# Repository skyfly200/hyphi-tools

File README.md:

# Hyphi Tools

Browser-based design tools for Hyphi's LED art, origami and print work, plus
the hardware pipeline for Hyphi boards. The web app is a single Vite build:
a React router shell, with the larger editors written in Vue and mounted
inside it. Everything runs client-side; there is no backend.

## Tools

| Route | Tool | What it does | Exports |
|-------|------|--------------|---------|
| `/qr` | **QRForge** | Styled QR codes: colors, dot shapes, logos, frames, many payload types (URL, Wi-Fi, vCard, SMS, ...), UTM campaign tags on URLs | PNG, JPG, SVG, multi-part STL zip for multi-material printing |
| `/fold` | **FoldPress** | Turns a `.fold` or SVG crease pattern into a pair of press plates for pre-creasing paper | STL |
| `/foldform` | **FoldForm** | Living-hinge origami models: rigid panels with flexible fold lines, optional SVG artwork as a multi-color design layer | STL zip (model plus front/back design layers) |
| `/foldstudio` | **FoldStudio** | Crease pattern editor on a dynamic grid with mirror, repeat and angle-defined creases; checks flat-foldability | FOLD |
| `/foldstudio/docs` | FoldStudio docs | User guide for FoldStudio | |
| `/polyforge` | **PolyForge** | Parametric polyhedral LED fixtures: pick a solid, set design rules, place LEDs and connectors, unfold to a flat PCB | DXF and KiCad board for fab, GLB/STL of the folded model, patch JSON |
| `/harness` | **Harness Calculator** | Plans LED stem wiring harnesses (core bends, power taps, data links, tip forks, wire twist) and builds a precut wire list | CSV cut list, GLB of the 3D view |

The home page (`/`) links to each tool, plus the link shortener at
[l.hyphi.art](https://l.hyphi.art), which lives in the `hyphi-links` repo.

FOLD-based tools hand designs to each other ("Open in ...") through
`sessionStorage`, and save projects and preferences to `localStorage`, so
nothing leaves the browser.

## Development

Needs Node 18+ (developed on Node 22).

```sh
npm install
npm run dev       # Vite dev server
npm run build     # production build into dist/
npm run preview   # serve the built dist/
```

Netlify builds with `npm run build`, publishes `dist/`, and rewrites every
path to `index.html` so client-side routes work (see `netlify.toml`).

## Layout

```
src/
  main.jsx, App.jsx        React entry and routes
  Home.jsx                 landing page / tool index
  QRForge.jsx              React tools (single-file components)
  FoldPress.jsx
  FoldForm.jsx
  FoldStudioDocs.jsx
  FoldStudio.jsx           React wrappers that mount a Vue app ("Vue islands")
  PolyForge.jsx
  HarnessCalculator.jsx
  foldstudio/              FoldStudio Vue app: components/, lib/ (geometry, FOLD I/O, faces, persistence)
  polyforge/               PolyForge Vue app: components/, lib/ (polyhedra, unfold, LEDs, DXF, KiCad, zip)
  harness/                 Harness Calculator Vue app (Vuetify) and 3D view
  lib/                     shared helpers: FOLD handoff, FoldForm persistence, crease palette
QRForge/                   earlier standalone drafts of the QR generator (not part of the build)
hardware/                  KiCad/Blender hardware pipeline (Python, not part of the web build)
```

To add a tool, create its component in `src/`, add a `<Route>` in
`src/App.jsx`, and add a card to the `TOOLS` list in `src/Home.jsx`. For a
Vue tool, follow the pattern in `src/PolyForge.jsx`: a React component that
owns a host `div` and dynamically imports a `mount.js` that mounts the Vue app
into it, so Vue only loads on that route.

## Hardware pipeline

`hardware/` holds the spec-driven KiCad pipeline for Hyphi boards (migrating
off EasyEDA): one `product.yaml` per product, a parts library builder
(`fetch_parts.py`, using `easyeda2kicad`) and a headless Blender renderer
(`render.py`). It's Python and runs separately from the web app. See
[hardware/README.md](hardware/README.md) for phases and setup.

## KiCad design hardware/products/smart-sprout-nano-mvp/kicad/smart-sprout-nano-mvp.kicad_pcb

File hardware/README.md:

# Hyphi Hardware

Spec-driven KiCad pipeline for Hyphi boards. One `product.yaml` per product is
the source of truth; scripts turn it into libraries, netlists, layouts,
enclosures and build receipts. Deliberately semi-automated: scripts do the
repeatable parts, a human routes the critical nets and signs off.

```
hardware/
  products/<product>/product.yaml   spec: outline, parts (LCSC), placement, enclosure, variants
  products/<product>/kicad/         KiCad project (imported or generated)
  libs/hyphi/                       project symbol/footprint/3D library (built from specs)
  scripts/                          pipeline scripts (fetch_parts.py, altium_to_spec.py, check_board.py, render.py)
  docs/                             how-tos
```

## Phases

| Phase | Goal | Status |
|-------|------|--------|
| 0 | Migrate GlowFlora Home (V2 prototype) from EasyEDA to KiCad, install JLCPCB tooling, draft the spec | **in progress** |
| 1 | Spec-to-netlist proof (SKiDL) on one subcircuit: the MT9700 current-limit section | not started |
| 2 | Board-to-enclosure: Build123d for the printable shell (STEP/STL), Blender for organic parts and renders, both reading the spec and the KiCad board export | render script ready |
| 3 | CI gates: `kicad-cli` ERC/DRC, Gerber/BOM/CPL export, LCSC pricing, cost rollup | not started |
| 4 | Generative variants from one spec | not started |

## Products

| Product | Spec | Source |
|---------|------|--------|
| Smart Sprout Nano MVP | [product.yaml](products/smart-sprout-nano-mvp/product.yaml) | spec generated from the EasyEDA Pro Altium export; [KiCad project](products/smart-sprout-nano-mvp/kicad/) imported in KiCad 10; `check_board.py` passes |
| GlowFlora Home | [product.yaml](products/glowflora-home/product.yaml) | hand-seeded from the wiki BOM |

To draft a spec for another board from an EasyEDA Pro Altium export:

```sh
python3 hardware/scripts/altium_to_spec.py "<export>/Smart Sprout/<board folder>" \
  --id <product-id> --name "<Product Name>" --out hardware/products/<product-id>/product.yaml
```

Check a KiCad board still matches its spec (outline, layer count, every
part's position, rotation and side; no KiCad install needed):

```sh
python3 hardware/scripts/check_board.py hardware/products/<id>/product.yaml hardware/products/<id>/kicad/<id>.kicad_pcb
```

## Phase 0 quick start

1. Follow [docs/phase0-migration.md](docs/phase0-migration.md) to install KiCad 10
   and the plugins and import the EasyEDA project.
2. Build the project parts library from the spec:

   ```sh
   pip install easyeda2kicad pyyaml
   python3 hardware/scripts/fetch_parts.py hardware/products/glowflora-home/product.yaml
   ```

   This runs `easyeda2kicad` for every LCSC part in the spec and writes
   symbols, footprints and STEP models into `hardware/libs/hyphi/`. It needs
   internet access to the EasyEDA/LCSC API.
3. `python3 hardware/scripts/fetch_parts.py --check <product.yaml>` validates the
   spec and prints the Basic/Extended part split without downloading anything.

## Blender

KiCad stays the source of the board; Blender consumes it. The split:

- **Build123d** makes anything that must fit and print (shell, battery bay,
  switch and USB openings), because its dimensions come straight from the spec.
- **Blender** handles organic or decorative geometry (petals, diffusers, the
  sculpted parts of a GlowFlora) and every render, so photos and geometry come
  from the same files.

Render the board (and any Blender-authored models listed under `render.models`):

```sh
kicad-cli pcb export glb --subst-models --include-tracks --include-pads \
  -o hardware/products/glowflora-home/kicad/glowflora-home.glb \
  hardware/products/glowflora-home/kicad/glowflora-home.kicad_pcb
pip install bpy pyyaml
python3 hardware/scripts/render.py hardware/products/glowflora-home/product.yaml --variant default
```

PNGs land in `products/<product>/build/renders/`. A variant can override any
`render` field, for example a different enclosure model or camera list.

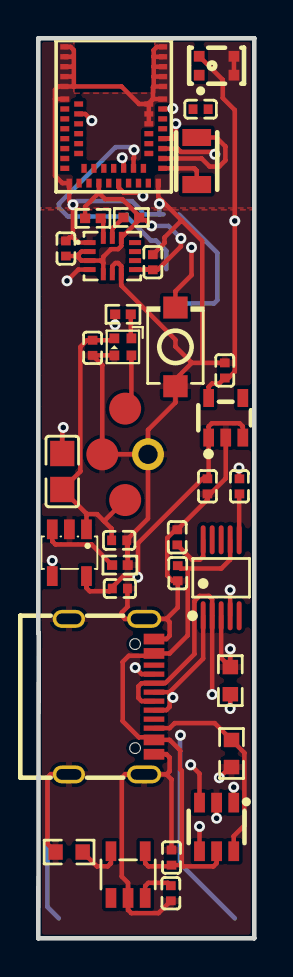
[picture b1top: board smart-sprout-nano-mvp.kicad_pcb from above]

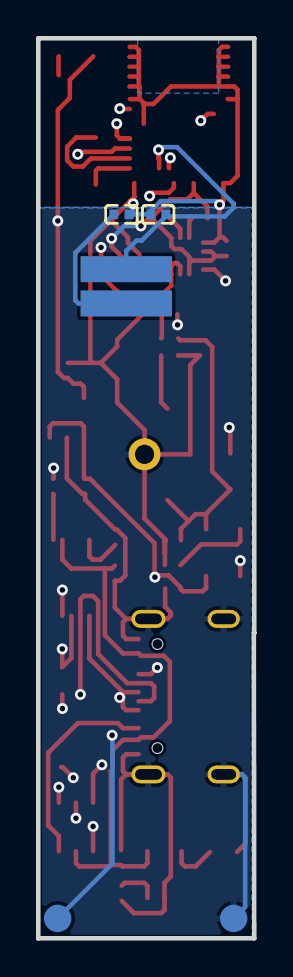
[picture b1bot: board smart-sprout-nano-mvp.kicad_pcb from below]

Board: 4 copper layers, 12.0 x 50.0 mm, 35 parts (2 on the bottom side), 27 nets.

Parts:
APP: SW-SMD_L3.9-W3.0-P4.45
C1, C2, C4, C5, C6, C7, C8, C9, C10, C11, C12, C13, C14, C15, C16: C0402
C3: C0805
D1: SOT-23-6_L2.9-W1.6-P0.95-LS2.8-BR
LED1: LED-SMD_4P-L1.5-W1.5-BL
M1: AN54LV-15
MIC1: MIC-SMD_4P-L2.8-W1.9-P1.84-TL_ZTS6117
R1, R2, R10: R0603
R6, R7, R14, R15: R0402
U1: MSOP-10_L3.0-W3.0-P0.50-LS5.0-BL
U2: SOT-23-5_L2.9-W1.6-P0.95-LS2.8-TL
U3: SOT-23-5_L3.0-W1.7-P0.95-LS2.8-BR
U4: SOT-23-5_L2.9-W1.6-P0.95-LS2.8-BR
U5: LGA-14_L3.0-W2.5-P0.50-TL
USB1: USB-C-SMD_GT-USB-7010E
X1: CRYSTAL-SMD_L3.2-W1.5

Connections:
$1N6708: LED1.1, R6.1
$1N12565: M1.24, R6.2
$1N16326: M1.25, U3.4
$1N17706: M1.33, X1.1
$1N17711: M1.32, X1.2
$1N18487: APP.2, M1.37
$1N18941: R7.1, U3.3
$1N18953: C13.1, M1.43
$2N1: D1.3, U1.1, USB1.A6, USB1.B6
$2N2: D1.1, U1.2, USB1.A7, USB1.B7
$2N11: R1.2, U2.5
$2N14: D1.6, R10.2, USB1.B5
$2N15: D1.4, R2.2, USB1.A5
$2N21: C10.2, U1.10
+5V: C4.1, C7.2, D1.5, U1.7, U2.4, USB1.A4B9, USB1.B4A9
DTR#: C13.2, U1.6
GND: APP.1, C1.2, C2.1, C3.1, C4.2, C5.2, C6.2, C7.1, C8.1, C9.1, C10.1, C11.1, C12.1, C14.1, C15.1, D1.2, LED1.3, M1.1, M1.15, M1.31, M1.40, M1.42, M1.44, M1.45, M1.46, M1.47, M1.48, M1.49, M1.50, M1.51, M1.52, M1.53, M1.54, M1.55, MIC1.2, MIC1.3, R1.1, R2.1, R7.2, R10.1, U1.3, U2.2, U3.2, U4.2, U5.1, U5.6, U5.7, USB1.1, USB1.2, USB1.3, USB1.4, USB1.A1B12, USB1.B1A12
INT1: M1.4, U5.4
NFC1: C8.2, M1.29
NFC2: C9.2, M1.27
RTS#: M1.35, U1.4
SCL: R14.2, U5.13
SDA: R15.2, U5.14
VBAT: C6.1, U2.3
VBATT: C1.1, C14.2, U3.5, U4.1, U4.3
VCC: C11.2, C12.2, C15.2, M1.20, MIC1.4, R14.1, R15.1, U4.5, U5.2, U5.3, U5.5, U5.8, U5.12
VLED: C2.2, C3.2, C5.1, LED1.2, U3.1

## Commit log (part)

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2026-04-16 Add QRForge tool
2026-04-17 Add .gitignore for node_modules and dist
    https://claude.ai/code/session_01VfCD3NQzr8GGxB5WpyrceK
2026-04-17 Add spacing between card name and subtitle
    https://claude.ai/code/session_01VfCD3NQzr8GGxB5WpyrceK
2026-04-17 Remove false no-tracking claim from link shortener card
    https://claude.ai/code/session_01VfCD3NQzr8GGxB5WpyrceK
2026-04-18 Make footer hyphi.art a link
    https://claude.ai/code/session_01VfCD3NQzr8GGxB5WpyrceK
2026-04-18 Read shortUrl param name from link shortener callback
    https://claude.ai/code/session_01VfCD3NQzr8GGxB5WpyrceK
2026-04-18 Fix logo transparency, icon visibility, grid width, and default preset
    - Skip QR dots in logo bounding box so icons render cleanly with no modules bleeding through
    - Icon cards in unselected state now use #ddddf0 (always-visible) instead of fgColor which could be black-on-black
    - Icon grid switched from 4 to 5 columns with tighter padding for narrower cards
    - Added "Default" (white on black) as the first color preset
    https://claude.ai/code/session_01VfCD3NQzr8GGxB5WpyrceK
2026-04-18 Embed icon SVGs inline; no image wrappers or backgrounds
    - Replace svgToDataURL with extractSVGInner (strips <svg> wrapper only)
    - Add IconSVG component that renders paths inline with color via CSS currentColor
    - Icon selection sets selectedIcon only; logo state is now custom-upload-only
    - buildSVG embeds icons as a scaled <g> with inline paths; <image> only for uploads
    - inLogo guard now checks logoEnabled && (logo || selectedIcon)
    - Logo controls (color, size, notice) conditioned on logo || selectedIcon
2026-04-18 Export multi-material STL as a zip with two separate files
    - generateSTL now returns {base, modules} instead of a combined string
    - makeZip: pure-JS ZIP writer (STORE method, CRC-32, no deps)
    - Multi-material download: qrcode.zip containing qrcode_base.stl + qrcode_modules.stl
    - Single-material download unchanged: qrcode.stl
    https://claude.ai/code/session_01VfCD3NQzr8GGxB5WpyrceK
2026-04-21 FoldPress: heightfield plates with proper ridges and grooves
    - Replaced ridge-only prism approach with a 200×200 heightfield grid per plate
    - Top plate: M=ridge, V=groove; Bottom plate: V=ridge, M=groove; F/U=ridge both
    - Clearance gaps only at vertices shared by both M and V edges (not every intersection)
    - Output is binary STL (50 bytes/tri) instead of ASCII — ~4MB per plate vs ~12MB
    - makeZip already handles Uint8Array so no changes needed there
    https://claude.ai/code/session_01VfCD3NQzr8GGxB5WpyrceK
2026-04-21 FoldPress: fix anti-diagonal triangulation spikes in STL
    Standard quad triangulation splits every cell along the (0,0)→(1,1)
    diagonal. When a fold line runs along the opposite diagonal, adjacent
    triangles get wildly mismatched heights, producing saw-tooth spikes.
    Fix: choose the split diagonal per cell so the edge with the smaller
    height difference is used as the shared axis.
    https://claude.ai/code/session_01VfCD3NQzr8GGxB5WpyrceK
2026-04-21 QRForge: link Stats button to specific short-link dashboard page
    https://claude.ai/code/session_01VfCD3NQzr8GGxB5WpyrceK
2026-04-23 Add alignment rails and asymmetric keying to FoldPress
    Bottom plate gains a rectangular guide-wall frame (4 outer wall boxes)
    so the top plate slides into position automatically — no manual paper
    pre-alignment. One corner of the frame has a raised square tab; the
    matching corner of the top plate has a raised pip, making the correct
    orientation unambiguous for any pattern, including symmetric ones.
    New UI controls: Alignment rails toggle + Rail height / Wall thickness /
2026-04-25 FoldForm: auto-clamp hinge thickness to never exceed paper thickness
    useEffect reduces hingeH whenever panelH drops below it. Hinge slider
    max is bound to panelH and the number input clamps on change, so the
    constraint is enforced from all three interaction paths.
    https://claude.ai/code/session_01VfCD3NQzr8GGxB5WpyrceK
2026-04-26 FoldForm: face color painter + .fold export + Origami Simulator link
    - computeFaces(): planar half-edge traversal finds all bounded face
    regions from the crease pattern graph (works for .fold and SVG input)
    - Faces auto-assigned distinct colors from a 10-color palette on load
    - Click any panel in the preview to select it, then use the color picker
    to paint it; fold lines remain drawn on top for reference
    - toFOLD(): exports vertices, edges, faces + faces_color as a valid
2026-05-07 Add city mode, block scale, NFC pocket, border frame, edge text, multi-part export, nozzle snap, keychain placement to QRForge
    New 3D features:
    - City Mode: random per-module heights (configurable min/max) for skyscraper look
    - Block Scale: shrink module footprint 50-100% to add gaps between dots
    - Invert QR: swap dark/light modules
    - Border Frame: separate raised lip body for multi-color printing
    - NFC Pocket: recessed cavity on bottom face for embedding NFC sticker
2026-05-07 FoldStudio: square paper corners, inset paper inside canvas for edge-grab margin
2026-05-07 FoldStudio: project save/load + persistent prefs + TopBar with file controls
    - localStorage persistence for grid, labels, current paint assignment
    - Save/Open/Delete projects (named, in-browser) with modal UI
    - New TopBar holds New/Save/Open/Import/Export FOLD/Export SVG
    - Sidebar trimmed to Grid + Labels (file controls moved up)
    - Toolbar reorganized: Draw+Select with icons, separator, Mirror+Rotate+Angle with icons
    - Inline SVG icon set (Icon.vue) used by both bars
2026-05-07 FoldStudio: fix T-junctions, real Simulator handoff, radial-edge snaps
    - addEdgeWithSplits / repairPlanarGraph now split existing edges when a new
    segment terminates on the interior of one (T-junction), so face computation
    produces a complete face graph instead of just the outer paper face
    - loadModel runs repairPlanarGraph so previously-saved patterns get cleaned up
    - Open in Simulator: download the .fold and open origamisimulator.org with
    clear drop-the-file instructions (the ?pattern=data: URL was never honored
2026-05-08 FoldStudio: mobile-friendly layout
    - Sidebar and Inspector collapse to off-canvas drawers below 900px wide,
    with toolbar toggle buttons (panelLeft / panelRight) and a tap-to-dismiss
    backdrop
    - Toolbar drops tool labels and bumps padding for touch-friendly tap targets
    - TopBar drops button labels at <=700px so the file controls fit
    - Modals constrain to viewport (max-width/height with overflow-y) and the
2026-05-08 FoldStudio: make Mirror selection click-to-toggle, highlight axis edge
    - Mirror tool now treats canvas clicks like additive selection (click to add,
    click again to remove), no shift needed — works on touch
    - When Mirror axis = "Selected edge", the first selected edge is rendered
    with an orange dashed overlay so the user can see which one is the axis
    - Apply Mirror disabled until >=2 edges selected when axis=edge
    - Cleaner hint text in the Tool options drawer
2026-05-08 FoldStudio: cleanup button + shared crease palette across all fold tools
    - New src/lib/foldPalette.js exports the canonical M/V/B/F/U stroke colors
    (and OS-specific colors) plus dash style. FoldForm, FoldPress and FoldStudio
    all import from it so the same .fold pattern renders identically across
    the three tools (M red, V blue, B near-black, F gray dashed, U muted)
    - cleanupRedundant model helper iteratively merges degree-2 vertices whose
    two incident edges share an assignment and lie ~180 degrees apart, plus
2026-05-09 FoldStudio: BottomBar for file actions, merged Export, templates modal, distinct icons, brighter boundary
    - New BottomBar.vue holds project actions: New (opens template modal),
    Cleanup, Save, Open, Import, Export (single button with .fold/.svg select,
    default FOLD), Simulator, FoldForm, FoldPress
    - TopBar slimmed to: brand + project + Tools toggle (mobile) + Snap + Help
    + Info toggle (mobile). All file-flow modals removed from TopBar
    - New NewProjectModal.vue + lib/templates.js with bases: Blank,
2026-05-09 FoldStudio: move Edges/Vertices/Both segmented control to the toolbar (visible while Select tool active)
2026-05-10 FoldStudio: drop rabbit-ear, pinch-zoom, mobile tooltip, status in bottom bar, select-mode icons
    Bundle: FoldStudio JS dropped from 99.5 KB → 47.9 KB gzipped (~52% smaller).
    - Replaced rabbit-ear's graph.populate with a self-contained planar face
    traversal in lib/faces.js. Same output for the patterns we care about;
    rabbit-ear removed from package.json
    - New Tooltip.vue listens for long-press (~500ms) on any [title] element
    and shows a centered toast above the touch point. Native title is
2026-05-12 FoldForm: drop Open-in-FoldPress; FoldStudio: mobile paint dropdown
    - FoldForm: removed the Open-in-FoldPress handoff button; only
    Edit-in-FoldStudio remains in the export row
    - FoldStudio mobile (<=900px): the five M/V/B/F/U paint buttons collapse
    into a single trigger button showing the active paint + chevron. Tap to
    open a small popover with all five options (color swatch + letter + full
    name). Tap an option to pick + close; tap outside to dismiss via a tiny
2026-05-12 FoldStudio: light/dark theme toggle + outlined Help swatches
    - Help modal swatches updated to the canonical EDGE_COLOR values and now
    carry a faint white outline so the darker B / U boxes are visible
    against the modal background
    - Light/dark theme switcher in the TopBar (sun/moon icon, persisted).
    Theme classes redeclare a wider set of CSS variables — including new
    --canvas-bg, --paper, --paper-stroke, --grid-line, --grid-node, --vertex
2026-05-12 FoldStudio: docs page, label rework, multi-select toggle, validation in Sidebar
    - New /foldstudio/docs route — full-page docs with TOC, mobile vs desktop
    comparison, every feature explained. Help modal gains an "Open full
    docs ↗" link that opens in a new tab
    - Labels reworked: instead of three independent V/E/F checkboxes, one
    type at a time via a segmented control (Off / V / E / F). New
    "Hover-only" option restricts the display to the label closest to the
2026-05-13 FoldStudio bases flat-foldable, FoldForm/FoldPress download race fix, clearer relief UI
    - Templates: Preliminary, Waterbomb and Radial bases ship with valid M/V
    assignments. Each flips one crease to satisfy Maekawa (preliminary
    5V+3M, waterbomb 5M+3V, radial 9M+7V at the centre). Square twist
    remains 'U' since its geometry needs extra pleats to fold flat.
    Smoke-tested: all six templates now report OK from
    validateFlatFoldability after load
2026-05-13 FoldForm: save/load projects, per-edge hinge widths, panel removal
    - New src/lib/foldFormPersistence.js — localStorage-backed save / load /
    list / delete / rename for FoldForm projects. Project payload includes
    pattern, faceColors, edgeHingeW, removedFaces, designSVG, designName,
    paperMM, panelH, hingeH, hingeW, designBaseH, designEmb
    - Project section in the L panel: Save / Open / Update buttons + name
    badge. Save modal accepts a name; Open modal lists projects with
2026-05-14 FoldStudio: T-junction + coincident / overlapping edge checks
    - New validateGeometry in rabbitear.js: flags three kinds of geometry
    issues:
    - tjunction: a vertex sits on the interior of an edge it doesn't end
    - duplicate: two edges share the same vertex pair
    - overlap: collinear edges that share a sub-segment along their length
    - Wired into runValidation with its own state.validateGeo toggle
2026-05-15 FoldStudio: construction tools + smart selection + drawer toolbar
    Toolbar refactor
    - New ToolDrawer.vue: reusable popover that groups a set of tools behind
    a single labelled trigger button. Clicking the trigger opens the
    popover; clicking a tool inside switches state.tool and closes the
    drawer. Trigger highlights when one of its tools is active.
    - Transform tools (Mirror / Rotate / Angle / Relief) and the new
